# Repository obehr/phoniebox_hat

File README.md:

# phoniebox_hat
Raspberry Pi HAT for [RPi-Jukebox-RFID](https://github.com/MiczFlor/RPi-Jukebox-RFID)

In 2021 I built a Raspberry PI based Jukebox with RFID reader (see [here](https://github.com/MiczFlor/RPi-Jukebox-RFID/discussions/1331#discussioncomment-433065)). I used a breadboard for buttons and LEDs, USB sound card, ground loop isolator, PAM8403 amplifier. To disconnect the Raspberry from its USB power bank supply on shutdown, I used the awesome [OnOff SHIM](https://shop.pimoroni.com/products/onoff-shim) by Pimoroni.

This is a Raspberry Pi HAT for the 40W GPIO header. It integrates all of those functions on a single custom PCB:
 - DAC (PCM5102a)
 - Amplifier (PAM8406)
 - LED open drain buffers
 - Button inputs with hardware debounce
 - Screw clamps for connecting buttons and LEDs
 - Pin headers for RFID-RC522 and I2C
 - Battery disconnect circuit (the OnOff SHIM is awesome but I didn't want a separate PCB)
 - USB-C connector for power supply

The PCB complies to the official [HAT specification](https://github.com/raspberrypi/hats). Schematic and layout are done in KiCad 6.0. When ordering five PCBs including assembly at JLCPCB, one board costs around 18 USD.

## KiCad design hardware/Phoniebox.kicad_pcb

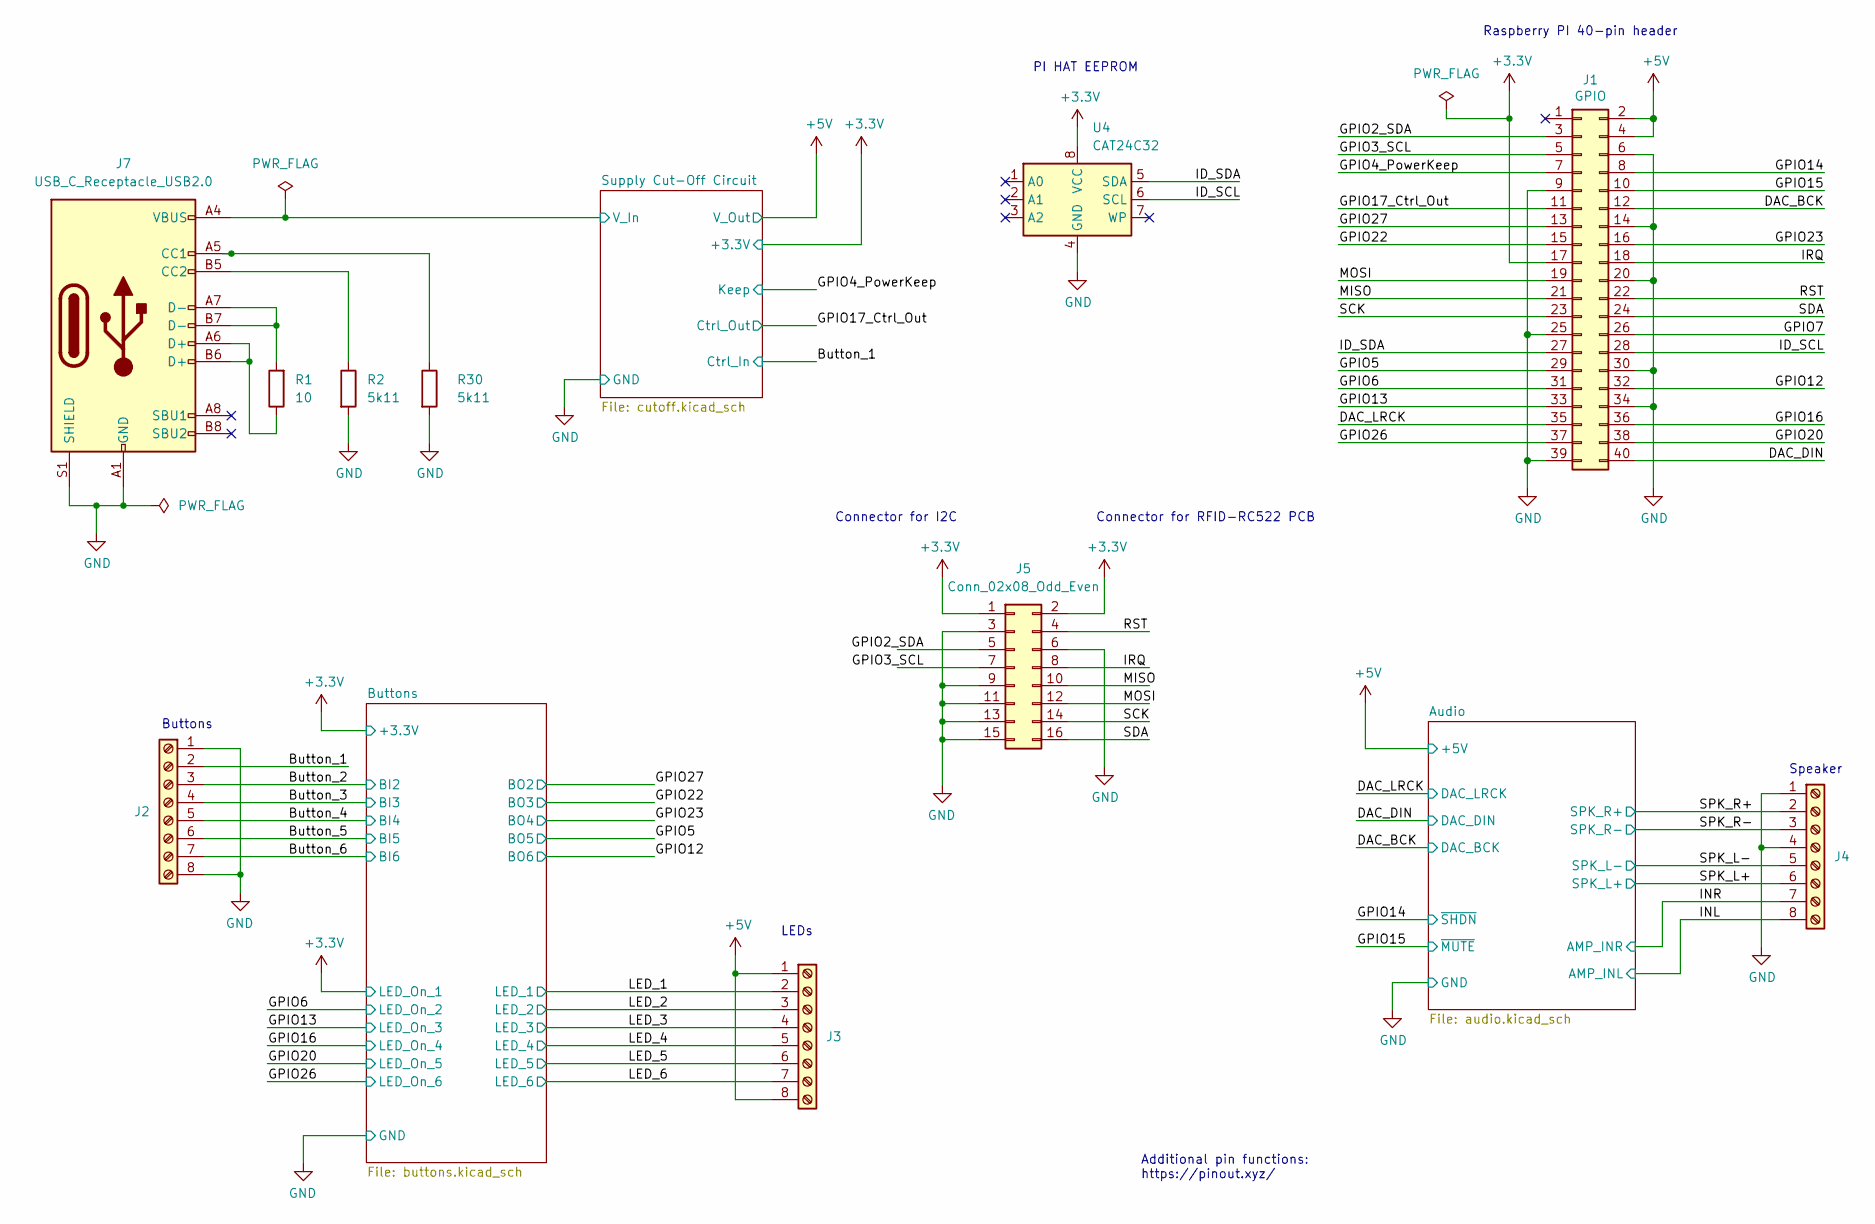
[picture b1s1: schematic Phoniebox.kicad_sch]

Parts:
J1: GPIO; PinSocket_2x20_P2.54mm_Vertical; LCSC C2977589
J2, J3, J4: Screw_Terminal_01x08; TerminalBlock_Phoenix_MPT-0,5-8-2.54_1x08_P2.54mm_Horizontal
J5: Conn_02x08_Odd_Even; PinHeader_2x08_P2.54mm_Vertical_SMD
J7: USB_C_Receptacle_USB2.0; USB_C_Receptacle_HRO_TYPE-C-31-M-12; LCSC C165948
R1: 10; R_0603_1608Metric
R2, R30: 5k11; R_0603_1608Metric
U4: CAT24C32; TSSOP-8_4.4x3mm_P0.65mm; LCSC C94264

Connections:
+3.3V: J1.17, J5.1, J5.2, U4.8 (VCC); also elsewhere on the board
+5V: J1.2, J1.4, J3.1, J3.8; also elsewhere on the board
/Button_1: J2.2; also elsewhere on the board
/Button_2: J2.3; also elsewhere on the board
/Button_3: J2.4; also elsewhere on the board
/Button_4: J2.5; also elsewhere on the board
/Button_5: J2.6; also elsewhere on the board
/Button_6: J2.7; also elsewhere on the board
/DAC_BCK: J1.12; also elsewhere on the board
/DAC_DIN: J1.40; also elsewhere on the board
/DAC_LRCK: J1.35; also elsewhere on the board
/GPIO2_SDA: J1.3, J5.5
/GPIO3_SCL: J1.5, J5.7
/GPIO4_PowerKeep: J1.7; also elsewhere on the board
/GPIO5: J1.29; also elsewhere on the board
/GPIO6: J1.31; also elsewhere on the board
/GPIO7: J1.26
/GPIO12: J1.32; also elsewhere on the board
/GPIO13: J1.33; also elsewhere on the board
/GPIO14: J1.8; also elsewhere on the board
/GPIO15: J1.10; also elsewhere on the board
/GPIO16: J1.36; also elsewhere on the board
/GPIO17_Ctrl_Out: J1.11; also elsewhere on the board
/GPIO20: J1.38; also elsewhere on the board
/GPIO22: J1.15; also elsewhere on the board
/GPIO23: J1.16; also elsewhere on the board
/GPIO26: J1.37; also elsewhere on the board
/GPIO27: J1.13; also elsewhere on the board
/ID_SCL: J1.28, U4.6 (SCL)
/ID_SDA: J1.27, U4.5 (SDA)
/INL: J4.8; also elsewhere on the board
/INR: J4.7; also elsewhere on the board
/IRQ: J1.18, J5.8
/LED_1: J3.2; also elsewhere on the board
/LED_2: J3.3; also elsewhere on the board
/LED_3: J3.4; also elsewhere on the board
/LED_4: J3.5; also elsewhere on the board
/LED_5: J3.6; also elsewhere on the board
/LED_6: J3.7; also elsewhere on the board
/MISO: J1.21, J5.10
/MOSI: J1.19, J5.12
/RST: J1.22, J5.4
/SCK: J1.23, J5.14
/SDA: J1.24, J5.16
/SPK_L+: J4.6; also elsewhere on the board
/SPK_L-: J4.5; also elsewhere on the board
/SPK_R+: J4.2; also elsewhere on the board
/SPK_R-: J4.3; also elsewhere on the board
/Supply Cut-Off Circuit/V_In: J7.A4 (VBUS), J7.A9 (VBUS), J7.B4 (VBUS), J7.B9 (VBUS); also elsewhere on the board
GND: J1.6, J1.9, J1.14, J1.20, J1.25, J1.30, J1.34, J1.39, J2.1, J2.8, J4.1, J4.4, J5.3, J5.6, J5.9, J5.11, J5.13, J5.15, J7.A1 (GND), J7.A12 (GND), J7.B1 (GND), J7.B12 (GND), J7.S1 (SHIELD), R2.2, R30.2, U4.4 (GND); also elsewhere on the board
unnamed: J7.A5 (CC1), R30.1
unnamed: J7.A6 (D+), J7.B6 (D+), R1.1
unnamed: J7.A7 (D-), J7.B7 (D-), R1.2
unnamed: J7.B5 (CC2), R2.1

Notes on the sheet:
Raspberry PI 40-pin header
Buttons
Additional pin functions: https://pinout.xyz/
LEDs
Connector for RFID-RC522 PCB
Speaker
PI HAT EEPROM
Connector for I2C

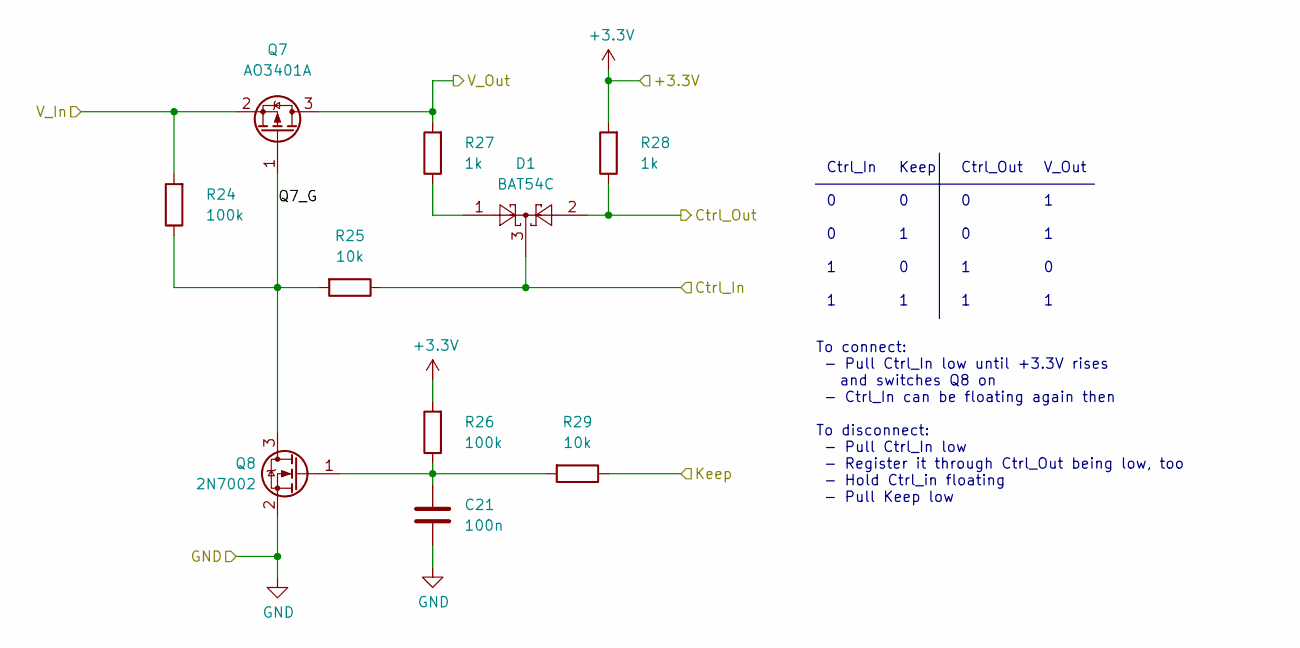
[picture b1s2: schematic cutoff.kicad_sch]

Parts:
C21: 100n; C_0603_1608Metric
D1: BAT54C; SOT-23; LCSC C37704
Q7: AO3401A; SOT-23; LCSC C15127
Q8: 2N7002; SOT-23; LCSC C350313
R24, R26: 100k; R_0603_1608Metric
R25, R29: 10k; R_0603_1608Metric
R27, R28: 1k; R_0603_1608Metric

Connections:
+3.3V: R26.2, R28.2; also elsewhere on the board
+5V: Q7.3 (D), R27.2; also elsewhere on the board
/Button_1: D1.3, R25.1; also elsewhere on the board
/GPIO4_PowerKeep: R29.1; also elsewhere on the board
/GPIO17_Ctrl_Out: D1.2, R28.1; also elsewhere on the board
/Supply Cut-Off Circuit/Q7_G: Q7.1 (G), Q8.3 (D), R24.1, R25.2
/Supply Cut-Off Circuit/V_In: Q7.2 (S), R24.2; also elsewhere on the board
GND: C21.2, Q8.2 (S); also elsewhere on the board
unnamed: C21.1, Q8.1 (G), R26.1, R29.2
unnamed: D1.1, R27.1

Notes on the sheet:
Ctrl_In 0 0 1 1
V_Out 1 1 0 1
Keep 0 1 0 1
Ctrl_Out 0 0 1 1
To connect: - Pull Ctrl_In low until +3.3V rises and switches Q8 on - Ctrl_In can be floating again then To disconnect: - Pull Ctrl_In low - Register it through Ctrl_Out being low, too - Hold Ctrl_in floating - Pull Keep low

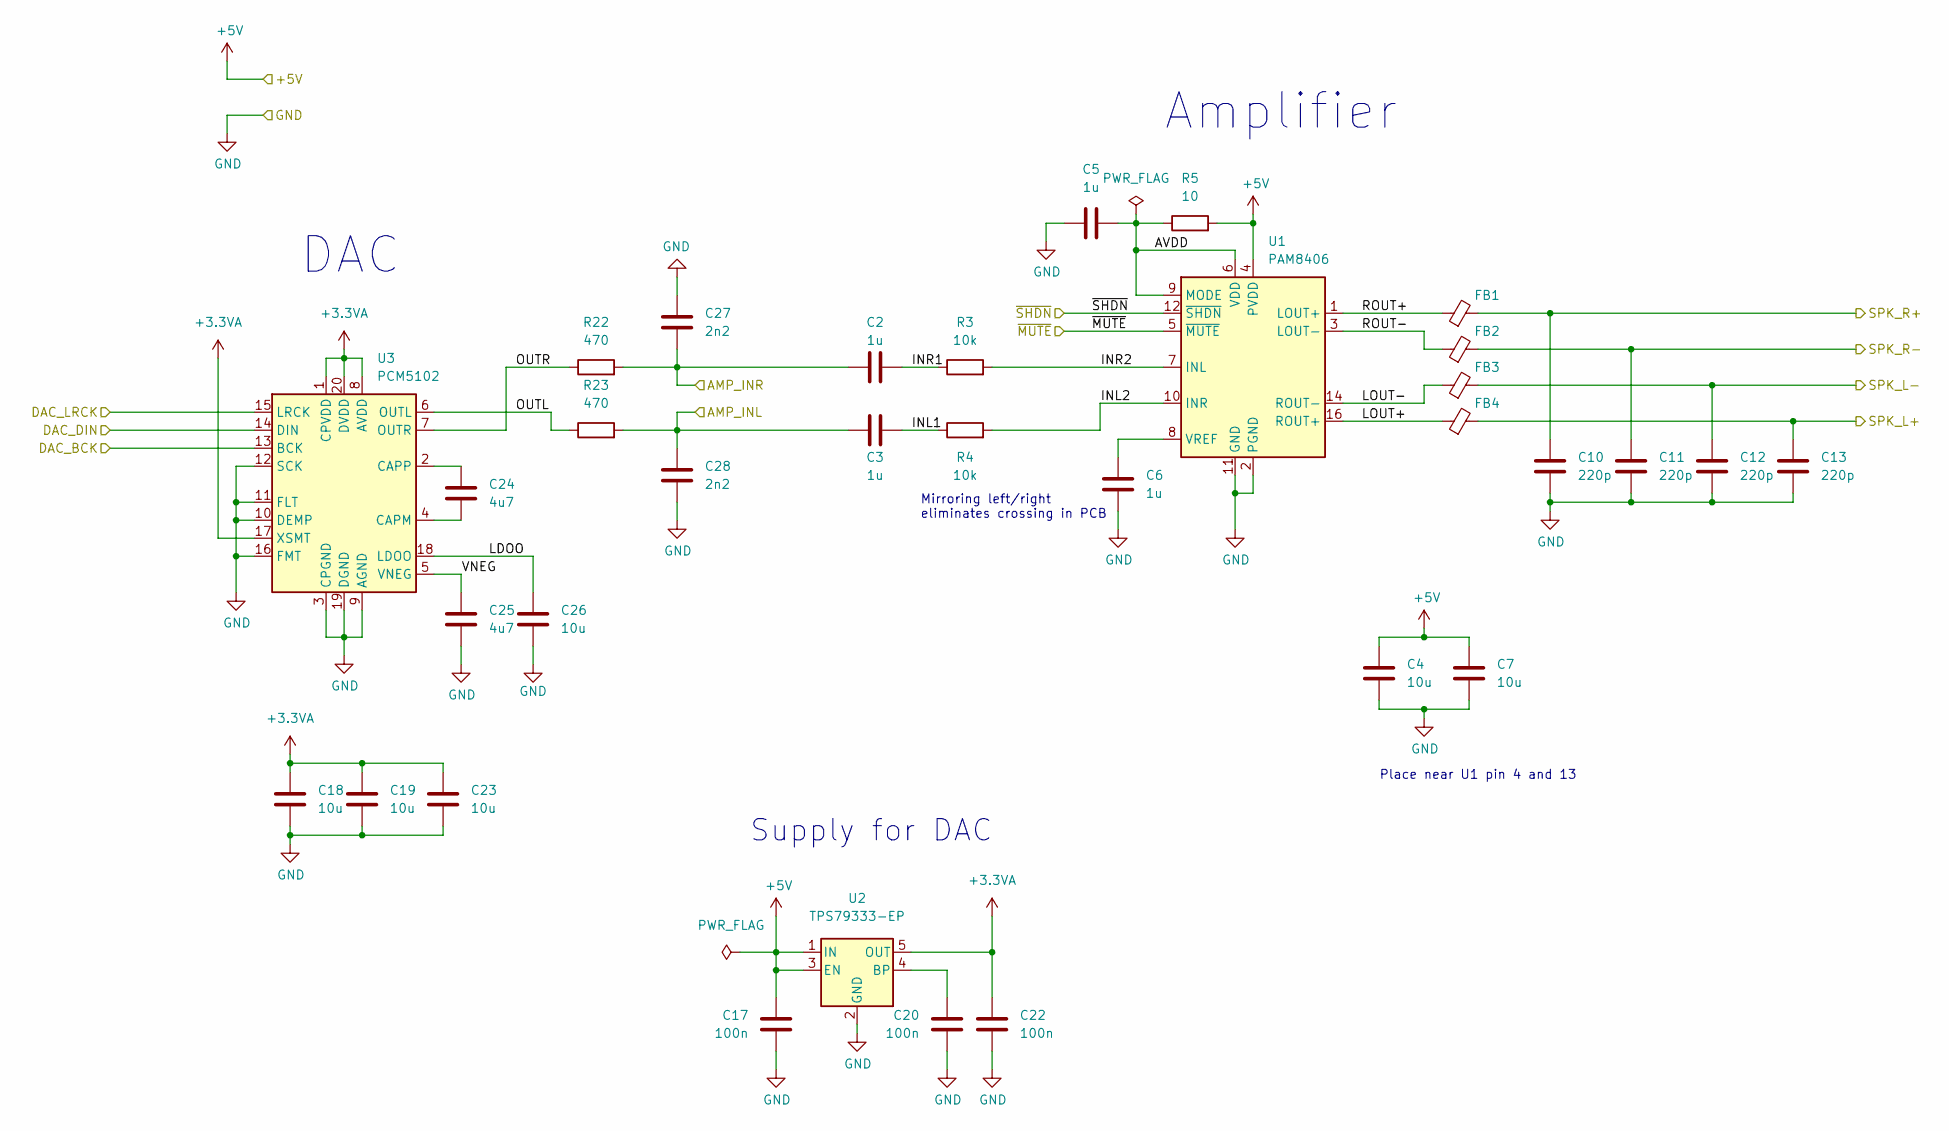
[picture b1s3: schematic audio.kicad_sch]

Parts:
C2, C3, C5, C6: 1u; C_0603_1608Metric
C4, C7, C18, C19, C23, C26: 10u; C_0805_2012Metric
C10, C11, C12, C13: 220p; C_0603_1608Metric
C17, C20, C22: 100n; C_0603_1608Metric
C24, C25: 4u7; C_0603_1608Metric
C27, C28: 2n2; C_0603_1608Metric
FB1, FB2, FB3, FB4: FerriteBead_Small; R_0603_1608Metric; LCSC C354394
R3, R4: 10k; R_0603_1608Metric
R5: 10; R_0603_1608Metric
R22, R23: 470; R_0603_1608Metric
U1: PAM8406; SOP-16_3.9x9.9mm_P1.27mm; LCSC C86270
U2: TPS79333-EP; SOT-23-5; LCSC C9840
U3: PCM5102; TSSOP-20_4.4x6.5mm_P0.65mm; LCSC C107671

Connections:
+3.3VA: C18.1, C19.1, C22.2, C23.1, U2.5 (OUT), U3.1 (CPVDD), U3.8 (AVDD), U3.17 (XSMT), U3.20 (DVDD)
+5V: C4.1, C7.1, C17.2, R5.2, U1.4 (PVDD), U1.13 (PVDD), U2.1 (IN), U2.3 (EN); also elsewhere on the board
/Audio/AVDD: C5.2, R5.1, U1.6 (VDD), U1.9 (MODE)
/Audio/INL1: C3.2, R4.1
/Audio/INL2: R4.2, U1.10 (INR)
/Audio/INR1: C2.2, R3.1
/Audio/INR2: R3.2, U1.7 (INL)
/Audio/LDOO: C26.1, U3.18 (LDOO)
/Audio/LOUT+: FB4.1, U1.16 (ROUT+)
/Audio/LOUT-: FB3.1, U1.14 (ROUT-)
/Audio/OUTL: R23.1, U3.6 (OUTL)
/Audio/OUTR: R22.1, U3.7 (OUTR)
/Audio/ROUT+: FB1.1, U1.1 (LOUT+)
/Audio/ROUT-: FB2.1, U1.3 (LOUT-)
/Audio/VNEG: C25.1, U3.5 (VNEG)
/DAC_BCK: U3.13 (BCK); also elsewhere on the board
/DAC_DIN: U3.14 (DIN); also elsewhere on the board
/DAC_LRCK: U3.15 (LRCK); also elsewhere on the board
/GPIO14: U1.12 (~SHDN); also elsewhere on the board
/GPIO15: U1.5 (~MUTE); also elsewhere on the board
/INL: C3.1, C28.1, R23.2; also elsewhere on the board
/INR: C2.1, C27.2, R22.2; also elsewhere on the board
/SPK_L+: C13.1, FB4.2; also elsewhere on the board
/SPK_L-: C12.1, FB3.2; also elsewhere on the board
/SPK_R+: C10.1, FB1.2; also elsewhere on the board
/SPK_R-: C11.1, FB2.2; also elsewhere on the board
GND: C4.2, C5.1, C6.2, C7.2, C10.2, C11.2, C12.2, C13.2, C17.1, C18.2, C19.2, C20.1, C22.1, C23.2, C25.2, C26.2, C27.1, C28.2, U1.2 (PGND), U1.11 (GND), U1.15 (PGND), U2.2 (GND), U3.3 (CPGND), U3.9 (AGND), U3.10 (DEMP), U3.11 (FLT), U3.12 (SCK), U3.16 (FMT), U3.19 (DGND); also elsewhere on the board
unnamed: C6.1, U1.8 (VREF)
unnamed: C20.2, U2.4 (BP)
unnamed: C24.1, U3.2 (CAPP)
unnamed: C24.2, U3.4 (CAPM)

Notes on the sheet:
DAC
Supply for DAC
Place near U1 pin 4 and 13
Mirroring left/right eliminates crossing in PCB
Amplifier

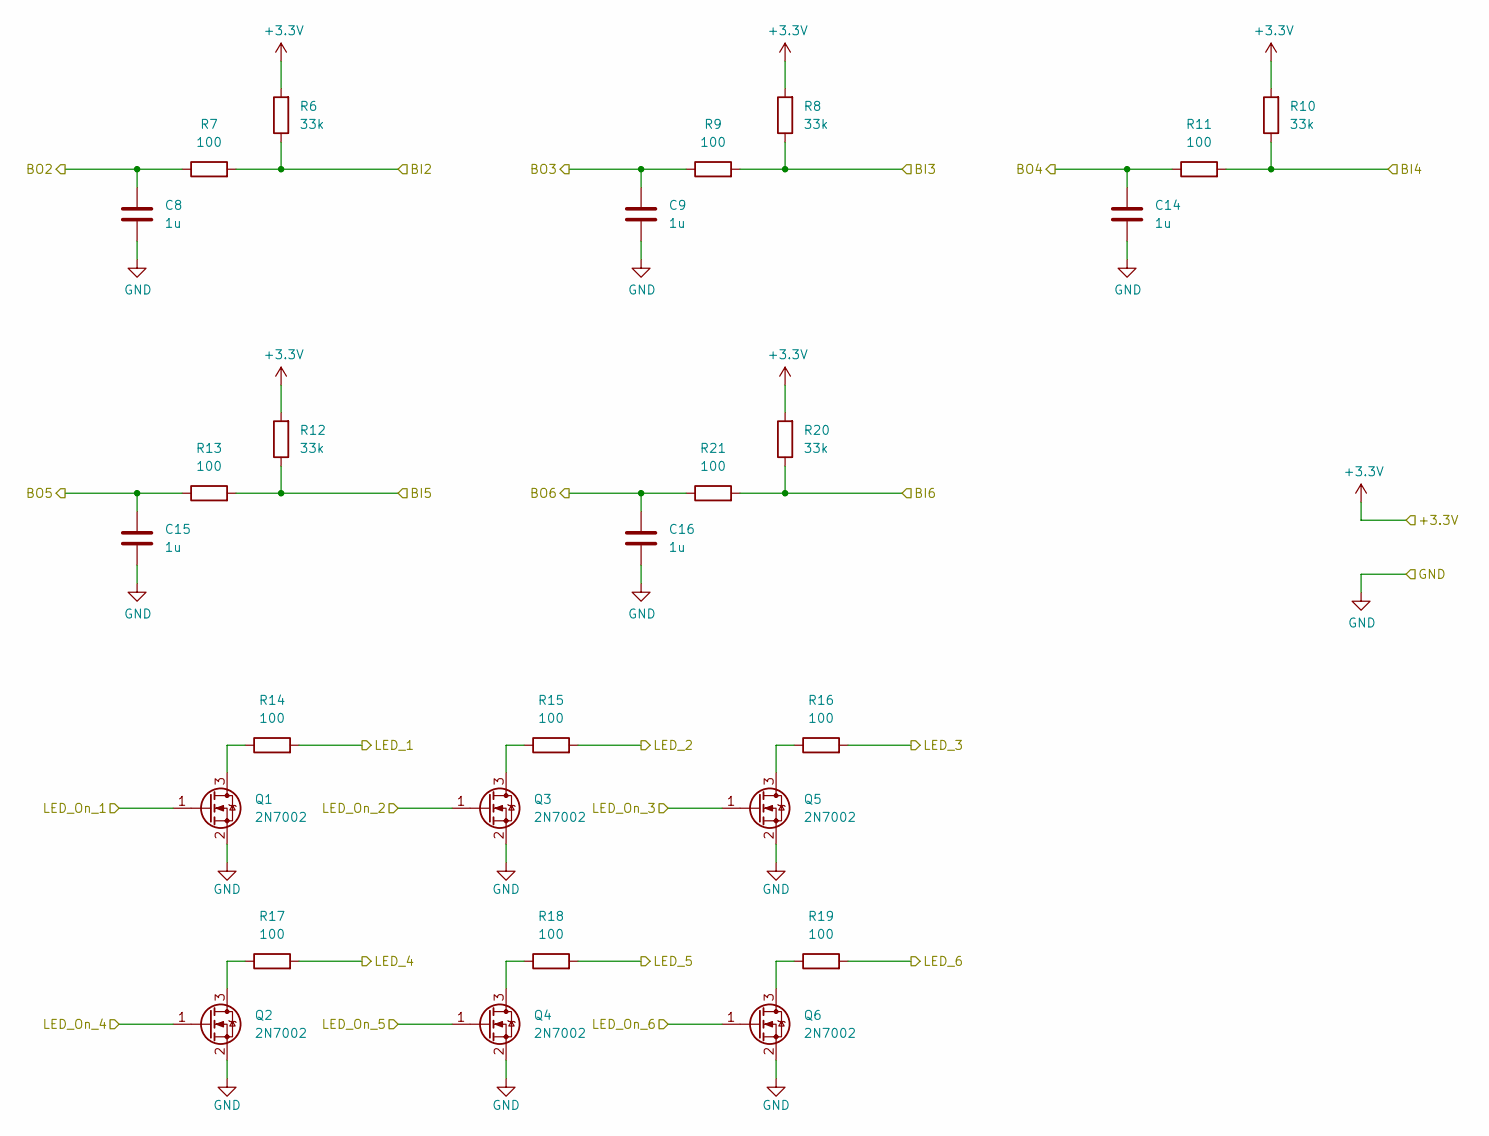
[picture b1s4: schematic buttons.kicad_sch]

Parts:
C8, C9, C14, C15, C16: 1u; C_0603_1608Metric
Q1, Q2, Q3, Q4, Q5, Q6: 2N7002; SOT-23; LCSC C350313
R6, R8, R10, R12, R20: 33k; R_0603_1608Metric
R7, R9, R11, R13, R14, R15, R16, R17, R18, R19, R21: 100; R_0603_1608Metric

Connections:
+3.3V: Q1.1 (G), R6.2, R8.2, R10.2, R12.2, R20.2; also elsewhere on the board
/Button_2: R6.1, R7.2; also elsewhere on the board
/Button_3: R8.1, R9.2; also elsewhere on the board
/Button_4: R10.1, R11.2; also elsewhere on the board
/Button_5: R12.1, R13.2; also elsewhere on the board
/Button_6: R20.1, R21.2; also elsewhere on the board
/GPIO5: C15.1, R13.1; also elsewhere on the board
/GPIO6: Q3.1 (G); also elsewhere on the board
/GPIO12: C16.1, R21.1; also elsewhere on the board
/GPIO13: Q5.1 (G); also elsewhere on the board
/GPIO16: Q2.1 (G); also elsewhere on the board
/GPIO20: Q4.1 (G); also elsewhere on the board
/GPIO22: C9.1, R9.1; also elsewhere on the board
/GPIO23: C14.1, R11.1; also elsewhere on the board
/GPIO26: Q6.1 (G); also elsewhere on the board
/GPIO27: C8.1, R7.1; also elsewhere on the board
/LED_1: R14.2; also elsewhere on the board
/LED_2: R15.2; also elsewhere on the board
/LED_3: R16.2; also elsewhere on the board
/LED_4: R17.2; also elsewhere on the board
/LED_5: R18.2; also elsewhere on the board
/LED_6: R19.2; also elsewhere on the board
GND: C8.2, C9.2, C14.2, C15.2, C16.2, Q1.2 (S), Q2.2 (S), Q3.2 (S), Q4.2 (S), Q5.2 (S), Q6.2 (S); also elsewhere on the board
unnamed: Q1.3 (D), R14.1
unnamed: Q2.3 (D), R17.1
unnamed: Q3.3 (D), R15.1
unnamed: Q4.3 (D), R18.1
unnamed: Q5.3 (D), R16.1
unnamed: Q6.3 (D), R19.1

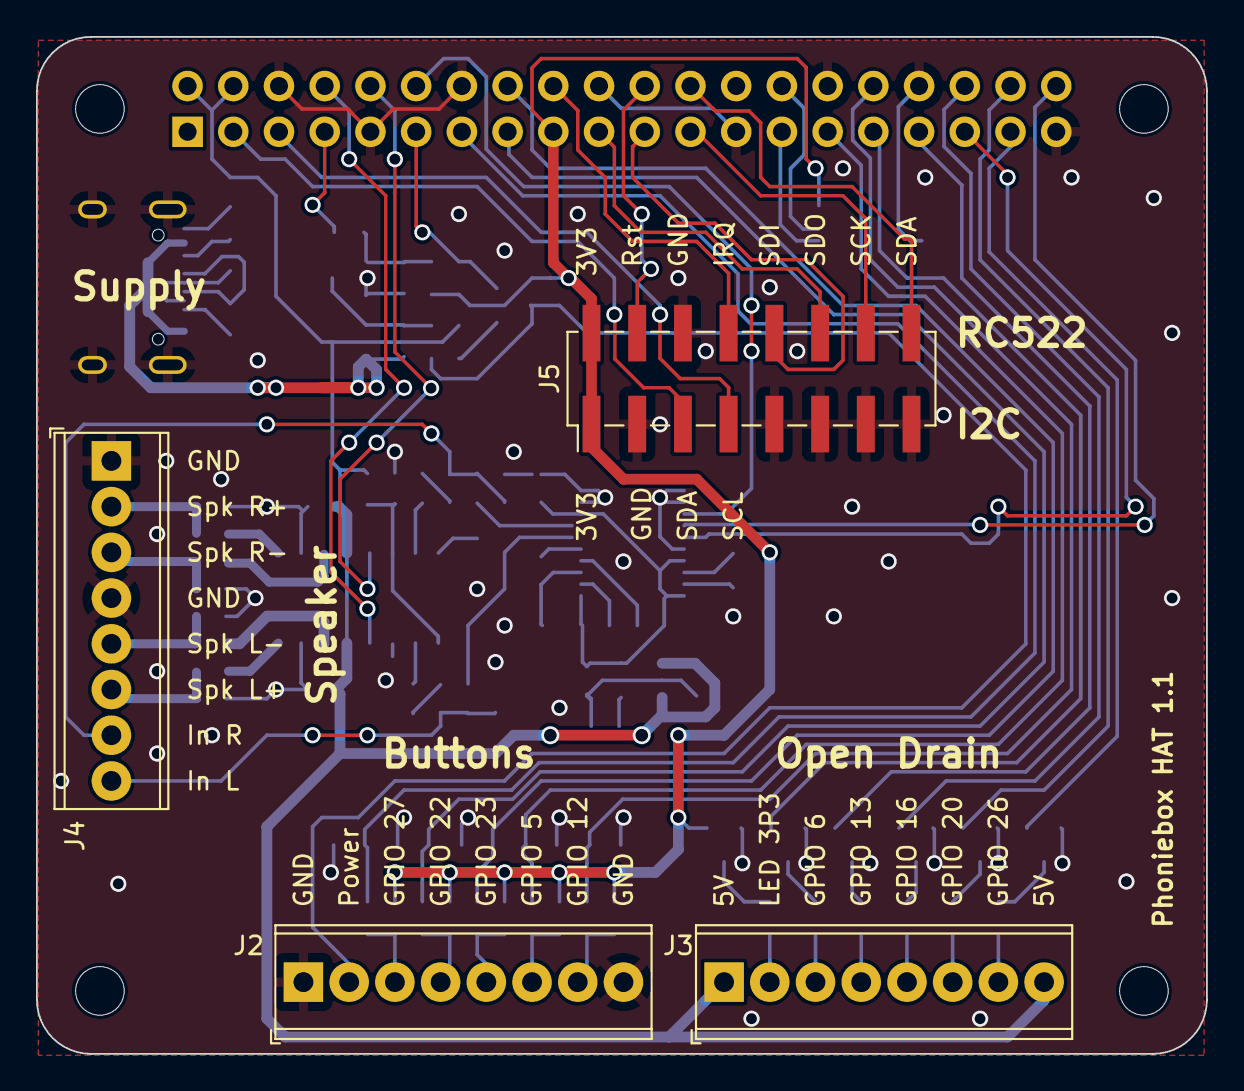
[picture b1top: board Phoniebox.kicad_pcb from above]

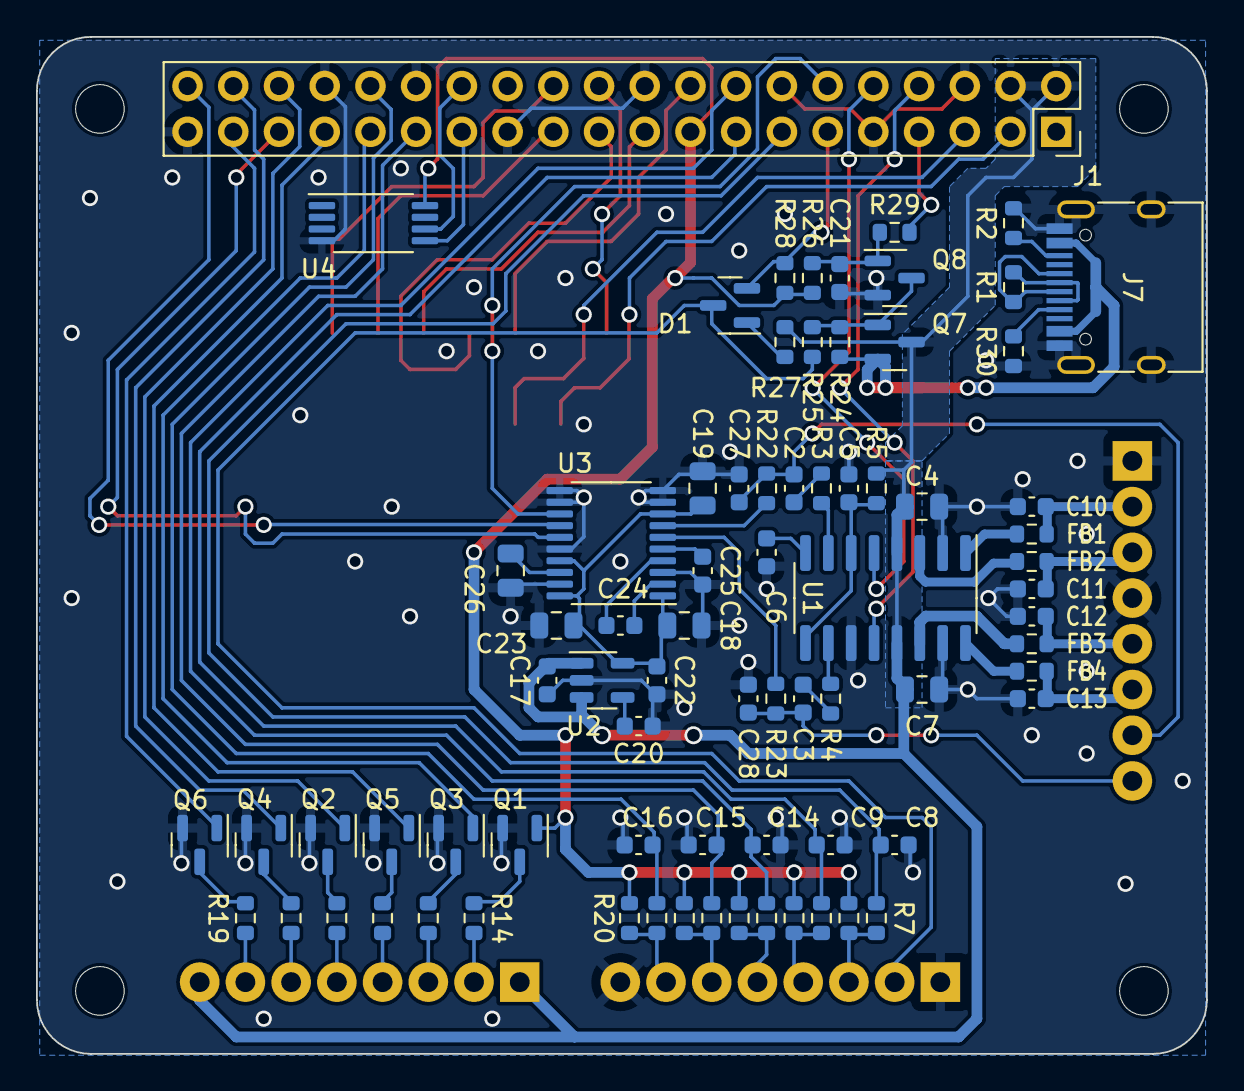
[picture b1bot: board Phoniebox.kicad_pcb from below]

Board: 2 copper layers, 65.0 x 56.5 mm, 84 parts (76 on the bottom side), 80 nets.

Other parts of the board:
MH1, MH2, MH3, MH4: MountingHole_2.7mm_M2.5

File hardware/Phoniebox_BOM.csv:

Comment,Designator,Footprint,LCSC
"220p","C10,C11,C12,C13","Capacitor_SMD:C_0603_1608Metric",""
"100n","C17,C20,C21,C22","Capacitor_SMD:C_0603_1608Metric",""
"1u","C2,C3,C5,C6,C8,C9,C14,C15,C16","Capacitor_SMD:C_0603_1608Metric",""
"4u7","C24,C25","Capacitor_SMD:C_0603_1608Metric",""
"2n2","C27,C28","Capacitor_SMD:C_0603_1608Metric",""
"10u","C4,C7,C18,C19,C23,C26","Capacitor_SMD:C_0805_2012Metric",""
"BAT54C","D1","Package_TO_SOT_SMD:SOT-23","C37704"
"FerriteBead_Small","FB1,FB2,FB3,FB4","Resistor_SMD:R_0603_1608Metric","C354394"
"GPIO","J1","Connector_PinSocket_2.54mm:PinSocket_2x20_P2.54mm_Vertical","C2977589"
"Screw_Terminal_01x08","J2,J3,J4","TerminalBlock_Phoenix:TerminalBlock_Phoenix_MPT-0,5-8-2.54_1x08_P2.54mm_Horizontal",""
"Conn_01x04_Male","J5","Connector_PinHeader_2.54mm:PinHeader_1x04_P2.54mm_Vertical_SMD_Pin1Left",""
"Conn_01x08_Male","J6","Connector_PinHeader_2.54mm:PinHeader_1x08_P2.54mm_Vertical_SMD_Pin1Left",""
"USB_C_Receptacle_USB2.0","J7","Connector_USB:USB_C_Receptacle_HRO_TYPE-C-31-M-12","C165948"
"2N7002","Q1,Q2,Q3,Q4,Q5,Q6,Q8","Package_TO_SOT_SMD:SOT-23","C350313"
"AO3401A","Q7","Package_TO_SOT_SMD:SOT-23"," C15127"
"10","R1,R5","Resistor_SMD:R_0603_1608Metric",""
"100","R11,R14,R15,R16,R17,R18,R19","Resistor_SMD:R_0603_1608Metric",""
"5k11","R2,R30","Resistor_SMD:R_0603_1608Metric",""
"470","R22,R23","Resistor_SMD:R_0603_1608Metric",""
"100k","R24,R26","Resistor_SMD:R_0603_1608Metric",""
"1k","R27,R28","Resistor_SMD:R_0603_1608Metric",""
"10k","R3,R4,R25,R29","Resistor_SMD:R_0603_1608Metric",""
"33k","R6,R7,R8,R9,R10,R12,R13,R20,R21","Resistor_SMD:R_0603_1608Metric",""
"PAM8406","U1","Package_SO:SOP-16_3.9x9.9mm_P1.27mm","C86270"
"TPS79333-EP","U2","Package_TO_SOT_SMD:SOT-23-5","C9840"
"PCM5102","U3","Package_SO:TSSOP-20_4.4x6.5mm_P0.65mm","C107671"
"CAT24C32","U4","Package_SO:TSSOP-8_4.4x3mm_P0.65mm","C94264"

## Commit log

2022-07-10 Add OnOff-SHIM circuit to PCB
2022-07-10 Fix DRC errors/warnings, Add round edges for PCB.
2022-07-10 Create hierachical schematic sheets for audio/LED/buttons.
2022-07-10 Place OnOffSHIM circuit on separate page.
2022-07-10 Update README.md
    Now complies to official HAT specification.
2022-07-10 Export schematic and PCB image
2022-07-10 Update README.md
    Add image
2022-07-11 Add I2C header for displays. Mute/SHDN now controlled by previously unused GPIO20/26. LED1 is now hardwired to ON=V3P3 high. GPIO7 would still be available to control LED1. Change debounce circuit to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
2022-07-11 Update README.md
    Now with I2C header.
2022-08-21 Add BOM descriptions and JLC PCB LCSC part numbers. Generate gerber, drill and pick-and-place files.
2022-08-27 Place on/off SHIM and EEPROM on bot
2022-09-27 Replace micro USB connector with USB-C type connector. DRC errors exist.
2022-09-28 Fixed gridd issues. Properly added USB-C connector. Fixed DRC errors.
2022-09-28 Update gerber files.
2022-09-29 Smaller high value caps. Standard R/C footprints instead of hand solder.
2022-09-29 Move a lot of parts. Switch audio l/r (only in schematic). Next step: Apply in PCB.
2022-10-01 Moved DAC. Replace pin headers with single row SMD ones (compatible with RC522/display PCBs to connect).
2022-10-01 Size 0805 for 10uF capacitors.
2022-10-01 Update PCB pic
2022-10-06 Add USB-C 3D model. Add pinning info in silkscreen for all connectors.
2022-10-21 Fix all ERC warnings. Replace 4u7 capacitor in cut-off circuit by 100 nF cap and 10 kOhm in series to reduce stress on Raspi GPIO.
2022-10-22 Update BOM
2022-11-18 Button resistors must be 100 Ohms
2022-11-20 Add documentation
2022-11-20 Replaced both single row connectors for RC522,I2C by one two row connector. Speaker left and right were mixed in top level schematic -> fixed net names and silkscreen text.
